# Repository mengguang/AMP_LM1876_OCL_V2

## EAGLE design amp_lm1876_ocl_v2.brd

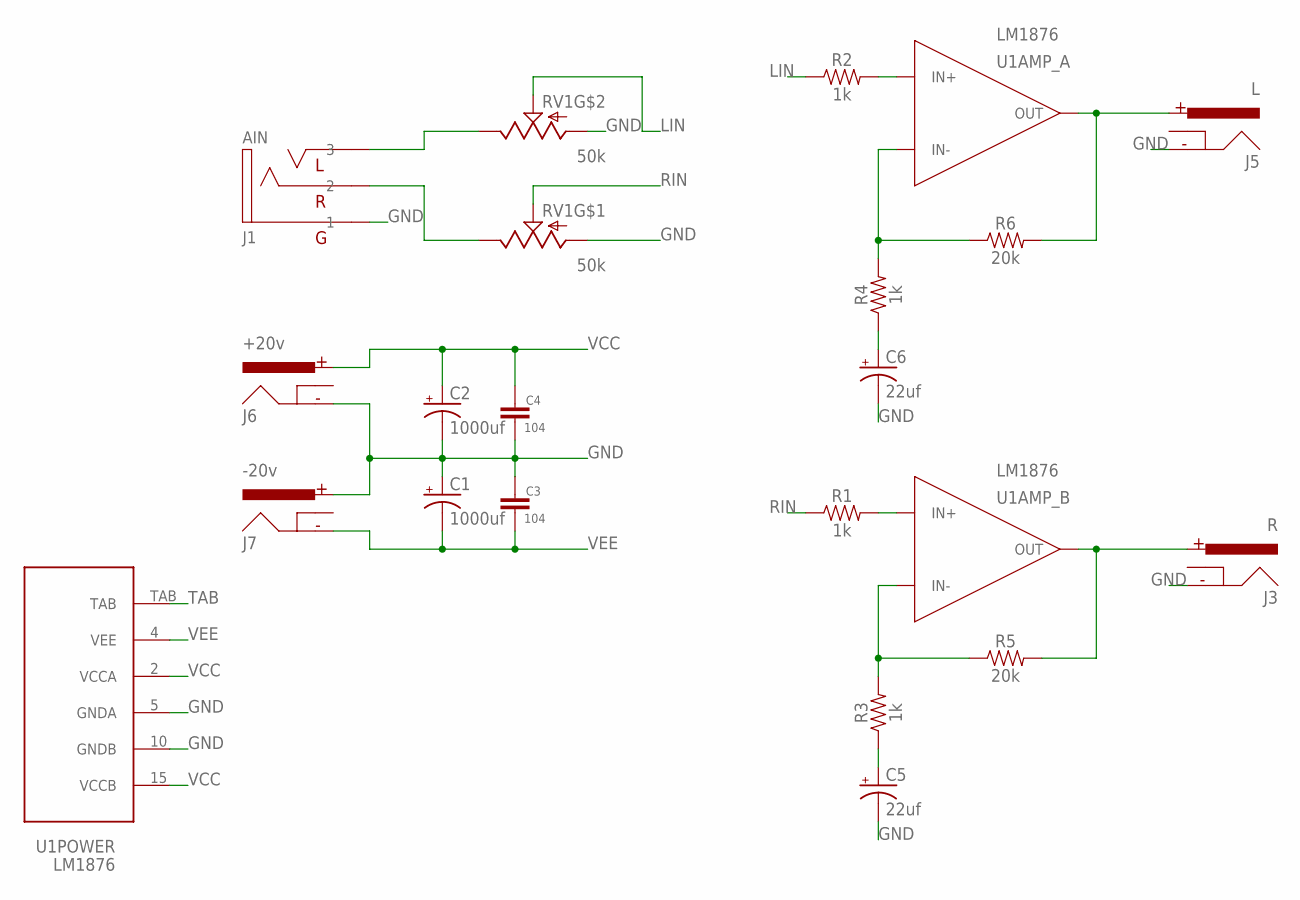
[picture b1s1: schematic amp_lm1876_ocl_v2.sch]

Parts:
C1, C2: 1000uf; CAP_5MM_10D
C3, C4: 104; C0603
C5, C6: 22uf; CAP_2.5MM
J1: AIN; 3.5MM
J3: R; POWER_JACK_PTH_LOCK
J5: L; POWER_JACK_PTH_LOCK
J6: +20v; POWER_JACK_PTH_LOCK
J7: -20v; POWER_JACK_PTH_LOCK
R1, R2, R3, R4: 1k; R0603
R5, R6: 20k; R0603
RV1: 50k; POT_DUAL_GREEN
U1: LM1876; MULTIWATT15_FLAT

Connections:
GND: C1.+, C2.-, C3.1, C4.2, C5.-, C6.-, J1.P$1 (1), J3.GND, J5.GND, J6.GND, J7.PWR, RV1.P$1 (A), RV1.P$4 (A), U1.5 (GNDA), U1.10 (GNDB)
LIN: R2.1, RV1.P$5 (S)
LOUT: J5.PWR, R6.2, U1.3 (OUT)
unnamed: R4.2, R6.1, U1.7 (IN-)
unnamed: R2.2, U1.8 (IN+)
unnamed: C6.+, R4.1
unnamed: R1.2, U1.13 (IN+)
unnamed: R3.2, R5.1, U1.12 (IN-)
unnamed: C5.+, R3.1
unnamed: J1.P$3 (3), RV1.P$6 (E)
unnamed: J1.P$2 (2), RV1.P$3 (E)
RIN: R1.1, RV1.P$2 (S)
ROUT: J3.PWR, R5.2, U1.1 (OUT)
TAB: U1.TAB
VCC: C2.+, C4.1, J6.PWR, U1.2 (VCCA), U1.15 (VCCB)
VEE: C1.-, C3.2, J7.GND, U1.4 (VEE)

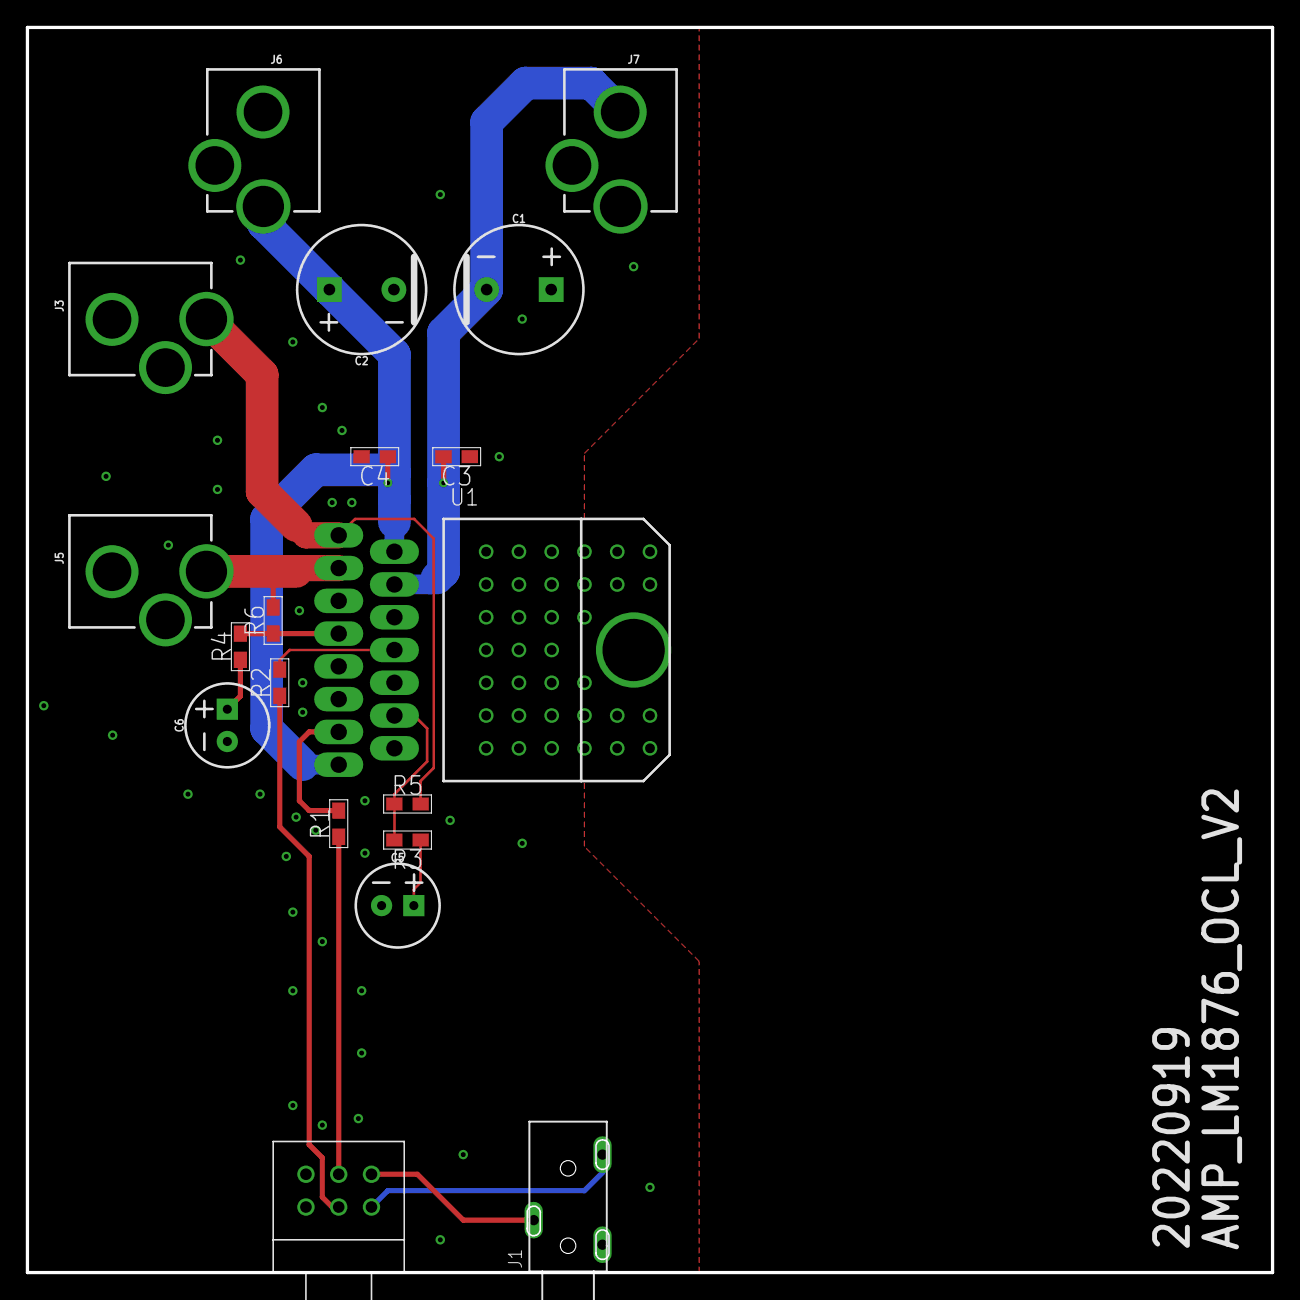
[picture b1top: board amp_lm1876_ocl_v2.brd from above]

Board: 2 copper layers, 96.5 x 96.5 mm, 19 parts (0 on the bottom side), 15 nets.

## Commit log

2022-09-29 20220919
